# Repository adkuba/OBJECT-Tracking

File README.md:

# OBJECTTracking

### Table of Contents
1. [What I've learned?](#what-Ive-learned)
2. [Android application](#android-application)
3. [IOS Application](#ios-application)
4. [Machine learning](#ml)
5. [Hardware](#hardware)
6. [Electronic board](#electronic-board)

## What I've learned?
* How to use **machine learning** to detect, track objects. How to build and train your own machine learning model and evolutional model. (**Python, Tensorflow, UnityML**)
* Building my own **Android** application that uses machine learning and camera. (**Java, Android Studio**)
* How to build simple **IOS** application that uses built in and external machine learning models, bluetooth and camera. (**Swift, XCode, OpenCV**)
* How to develop from the ground up, special **electronic board** that uses bluetooth. (**Silicon Labs, C**)

#### [Android application](APPS/Android/)
In Java works with SDK wersion 28 - Android 9. Application uses tensorflow model to detect objects and allows user to record videos from the camera. You can also click on object and it shows all the pictures of the same category objects in frame. Good base for developing visual machine learning solutions. <br>
Some errors with older Huawei phones. Optimalization [posibilities](https://developers.google.com/ml-kit/). I also share compressed (quantitized) Tensorflow lite model in application resources folder. (*ssd_mobilenet_v2_quantized_coco*)

#### [IOS application](APPS/IOS/)
IOS application. Compiled OpenCV 4.0.0 framework with trackers avaiable [here](https://www.dropbox.com/s/0iqwqfjz95ehut5/opencv2.framework.zip?dl=0) add it to Frameworks in XCode project settings. You can compile framework yourself following tutorial in official page but remember to add tracking package! Framework should be in main project folder (CamTracking2), can be changed in build settings. You can also follow this [tutorial](https://medium.com/@yiweini/opencv-with-swift-step-by-step-c3cc1d1ee5f1) Aplication allows to test OpenCV trackers, connect to Bluetooth devices and record videos. No suport for Vision tracking so far.

#### [ML](ML/)
Machine learning. Folder with files for creating special object comparison net, running different nets and collecting data. Everything using Keras and Tensorflow. Useful as example to work with.
* **[my_net.py](ML/my_net.py)** <br>
Using keras you can quickly create, train and deploy ready to use model of special net. It is developed for comparing the similarity of two pictures. I also share trained model on car pictures. Aproximately 5k images, 85% accuracy, 350 epochs. 

* **[data.py](ML/data.py)** <br>
Script in python using OpenCV to create set of 2 images either similar or different from video file. All commands in terminal. It needs preprocessed video to display pictures - file *process.py* uses Tensorflow model *mask_rcnn_inception_v2_coco*. Shows pictures of desired category objects from one frame and next. User needs to point which are similar, sets are created automaticly. Screenshot below - second picture.
* **[webpage](ML/webpage/)** <br>
Simple webpage that enables data collection similar to data.py but with progress save. Some improvements can be done. It needs preprocessed video to display pictures - file *process.py*. Webpage creates text file that should look like that 1-2,2-1 it means the same objects are 1 from first picture and 2 from second, 2 from first and 1 from second. Bad matches are created automaticly. Then we can create set of images with *webdecoder.py*. Folder structure without pictures as in repository. Screenshot below - first picture.
* **[run.py](ML/run.py)** <br>
File containing code for running different kinds of neural nets. Mask rcnn object detection, mobilenet_v2 classifier, ssd mobilenet_v2 object detector and Tensorflow Lite model.

#### 

#### Hardware

Simple device to use with mobile phones. All parts were designed in Inventor Proffesional and then 3D printed. Lower part has special thread used in almost all photography devices. We can easily mount it to, for example tripod. Inside the device, is place for all the electronics. I choosed Arduino Nano, Bluetooth for connection and stepper motor. The last one was a mistake. Much better would be the brushless motor used widely in camera gimbals. Upper part has a simple mount for smartphones, wich works with almost all models.

#### [Electronic board](ELECTRONIC-BOARD/)

Using Silicon Labs chip I developed special electronic board that uses Bluetooth. The goal was to implement [AoA in Bluetooth 5.1](https://www.silabs.com/products/wireless/learning-center/bluetooth/bluetooth-direction-finding), but unfortunatelly I wasn't able to achieve that. However I learned how to project board using Eagle from Autodesk and low level programing in Silicon Labs and C. Read [board.pdf](https://github.com/adkuba/OBJECTTracking/blob/master/board.pdf) to learn more about the idea.

Icons credits: 
[link1](https://www.flaticon.com/authors/freepik) 
[link2](https://www.flaticon.com/authors/pause08) 
[link3](https://www.flaticon.com/authors/smashicons)

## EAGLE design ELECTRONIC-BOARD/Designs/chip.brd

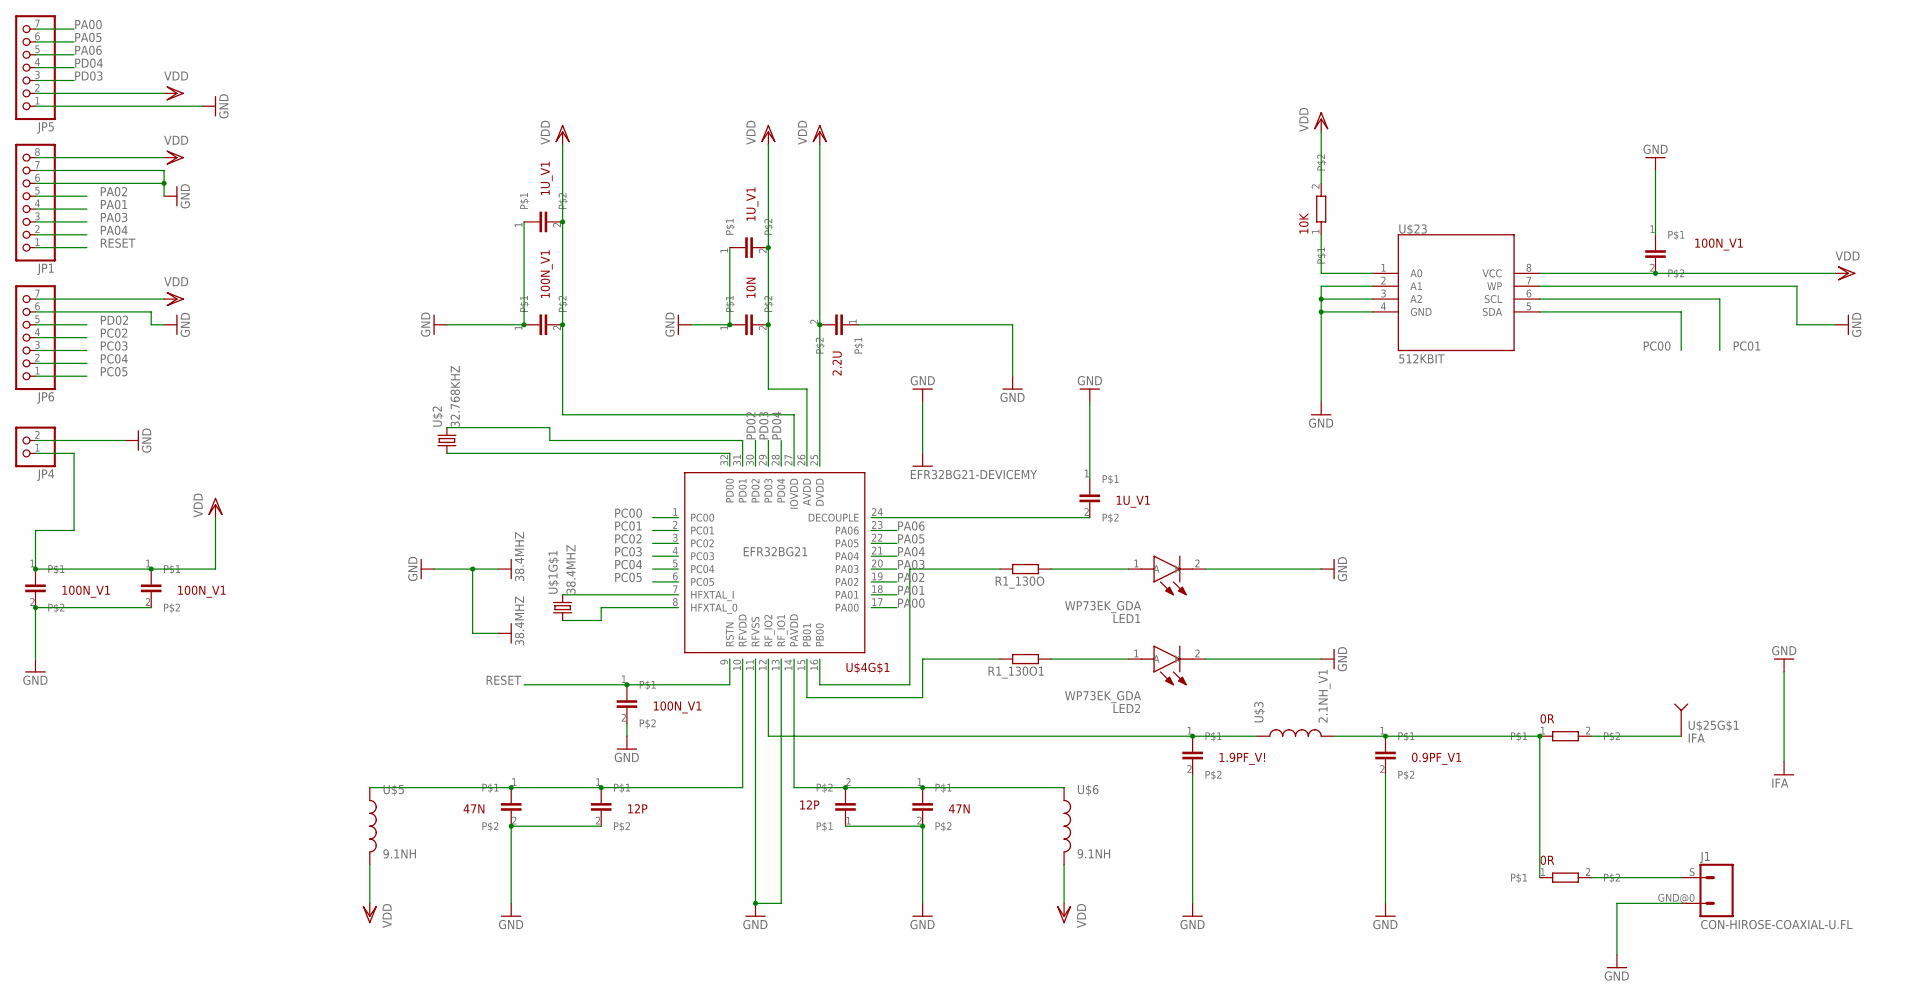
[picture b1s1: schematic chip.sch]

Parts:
J1: CON-HIROSE-COAXIAL-U.FL; CON-U.FL
JP1: PINHD-1X8; 1X08
JP4: PINHD-1X2; 1X02
JP5, JP6: PINHD-1X7; 1X07
LED1, LED2: WP73EK_GDA; WP73EKGDA
R1_130O, R1_130O1: R-EU_0204/7; 0204/7
U$1: 38.4MHZ; OSCCC200X160X40N
U$2: 32.768KHZ; RESC3213X90N
U$3: 2.1NH_V1; INDC0402X30N
U$4: EFR32BG21-DEVICEMY; QFN40P400X400X90-33T270N
U$5, U$6: 9.1NH; INDC0603X40N
U$7, U$8, U$9, U$10, U$22: 100N_V1; CAPC2012X78N
U$11: 0.9PF_V1; CAPC1005X50N
U$12: 1.9PF_V!; CAPC1005X50N
U$13, U$14: 47N; CAPC2012X78N
U$15, U$16: 12P; CAPC1005X50N
U$17: 2.2U; CAPC2012X125N
U$18, U$19, U$20: 1U_V1; CAPC2012X125N
U$21: 10N; CAPC2012X78N
U$23: 512KBIT; SOIC127P599X175-8N
U$24: 10K; RESC3213X90N
U$25: IFA
U$26, U$27: 0R; RESC3213X90N

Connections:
GND: J1.GND@0 (2), JP1.6, JP1.7, JP4.2, JP5.1, JP6.6, LED1.2 (K), LED2.2 (K), U$1.2 (GND), U$1.4 (GND), U$4.11 (RFVSS), U$4.13 (RF_IO1), U$4.33 (GND), U$7.2, U$8.1, U$9.1, U$10.2, U$11.2, U$12.2, U$13.2, U$14.2, U$15.2, U$16.1, U$17.1, U$18.1, U$19.1, U$20.1, U$21.1, U$22.2, U$23.2 (A1), U$23.3 (A2), U$23.4 (GND), U$23.7 (WP), U$25.P$2 (GND)
unnamed: U$1.3 (2), U$4.7 (HFXTAL_I)
unnamed: U$1.1, U$4.8 (HFXTAL_0)
unnamed: LED1.1 (A), R1_130O.1
unnamed: U$4.14 (PAVDD), U$6.1, U$14.1, U$16.2
unnamed: U$4.10 (RFVDD), U$5.1, U$13.1, U$15.1
unnamed: U$3.1, U$4.12 (RF_IO2), U$12.1
unnamed: U$3.2, U$11.1, U$26.1, U$27.1
unnamed: J1.S (1), U$27.2
unnamed: U$25.P$1 (ANTENNA), U$26.2
unnamed: U$4.24 (DECOUPLE), U$19.2
unnamed: U$2.2, U$4.31 (PD01)
unnamed: U$2.1, U$4.32 (PD00)
unnamed: LED2.1 (A), R1_130O1.1
unnamed: R1_130O.2, U$4.16 (PB00)
unnamed: R1_130O1.2, U$4.15 (PB01)
unnamed: U$23.1 (A0), U$24.1
PA00: JP5.7, U$4.17 (PA00)
PA01: JP1.4, U$4.18 (PA01)
PA02: JP1.5, U$4.19 (PA02)
PA03: JP1.3, U$4.20 (PA03)
PA04: JP1.2, U$4.21 (PA04)
PA05: JP5.6, U$4.22 (PA05)
PA06: JP5.5, U$4.23 (PA06)
PC00: U$4.1 (PC00), U$23.5 (SDA)
PC01: U$4.2 (PC01), U$23.6 (SCL)
PC02: JP6.4, U$4.3 (PC02)
PC03: JP6.3, U$4.4 (PC03)
PC04: JP6.2, U$4.5 (PC04)
PC05: JP6.1, U$4.6 (PC05)
PD02: JP6.5, U$4.30 (PD02)
PD03: JP5.3, U$4.29 (PD03)
PD04: JP5.4, U$4.28 (PD04)
RESET: JP1.1, U$4.9 (RSTN), U$10.1
VDD: JP1.8, JP4.1, JP5.2, JP6.7, U$4.25 (DVDD), U$4.26 (AVDD), U$4.27 (IOVDD), U$5.2, U$6.2, U$7.1, U$8.2, U$9.2, U$17.2, U$18.2, U$20.2, U$21.2, U$22.1, U$23.8 (VCC), U$24.2

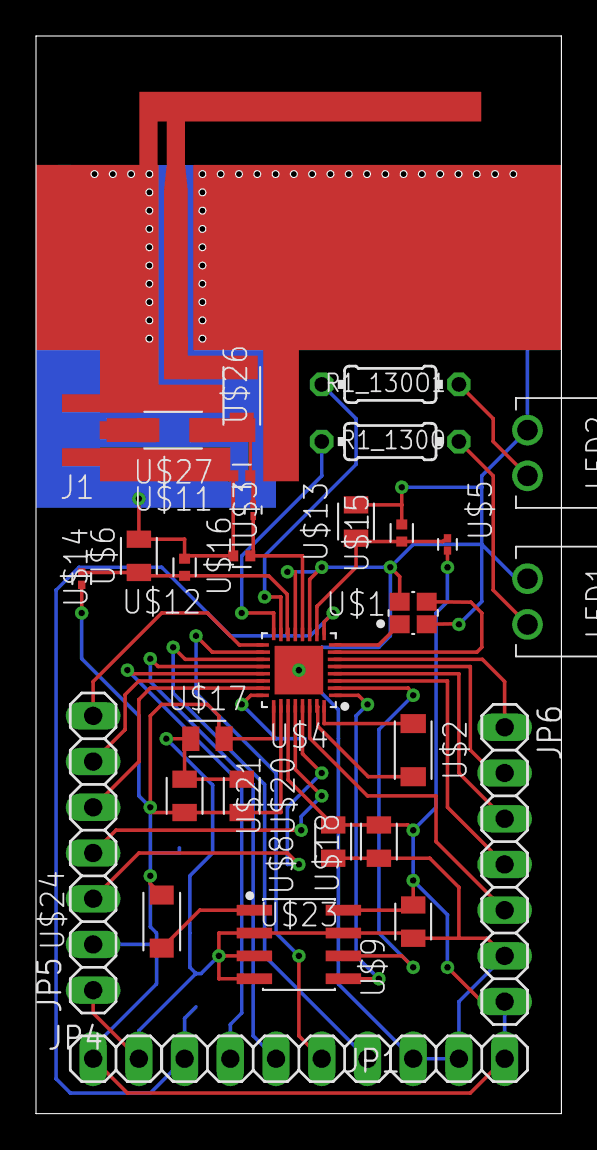
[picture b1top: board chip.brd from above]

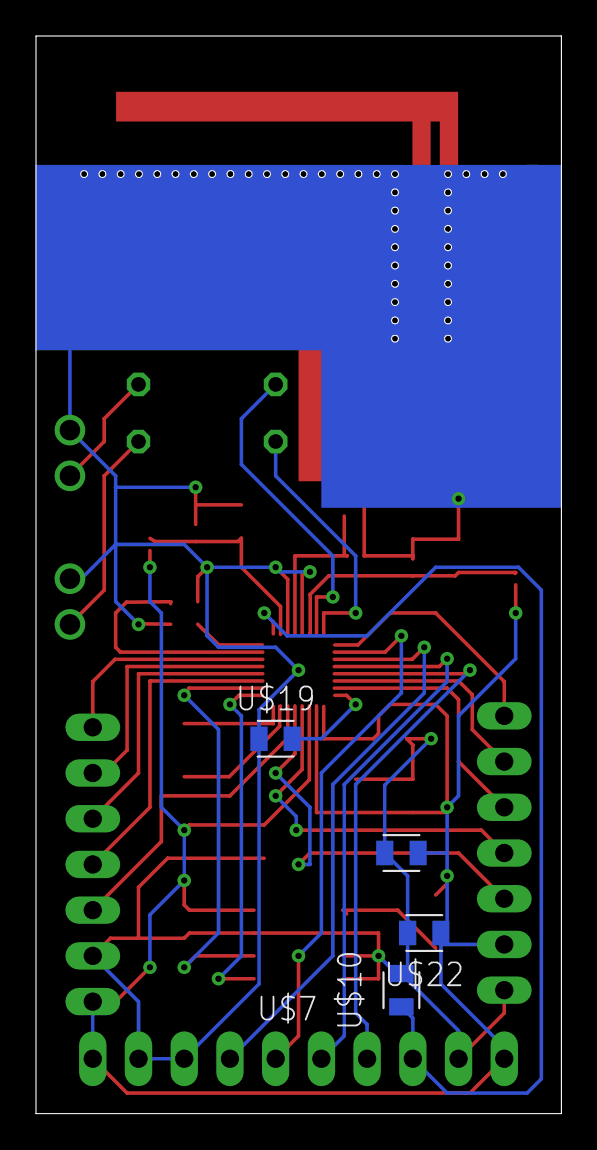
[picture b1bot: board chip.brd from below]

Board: 2 copper layers, 29.2 x 59.9 mm, 36 parts (4 on the bottom side), 35 nets.

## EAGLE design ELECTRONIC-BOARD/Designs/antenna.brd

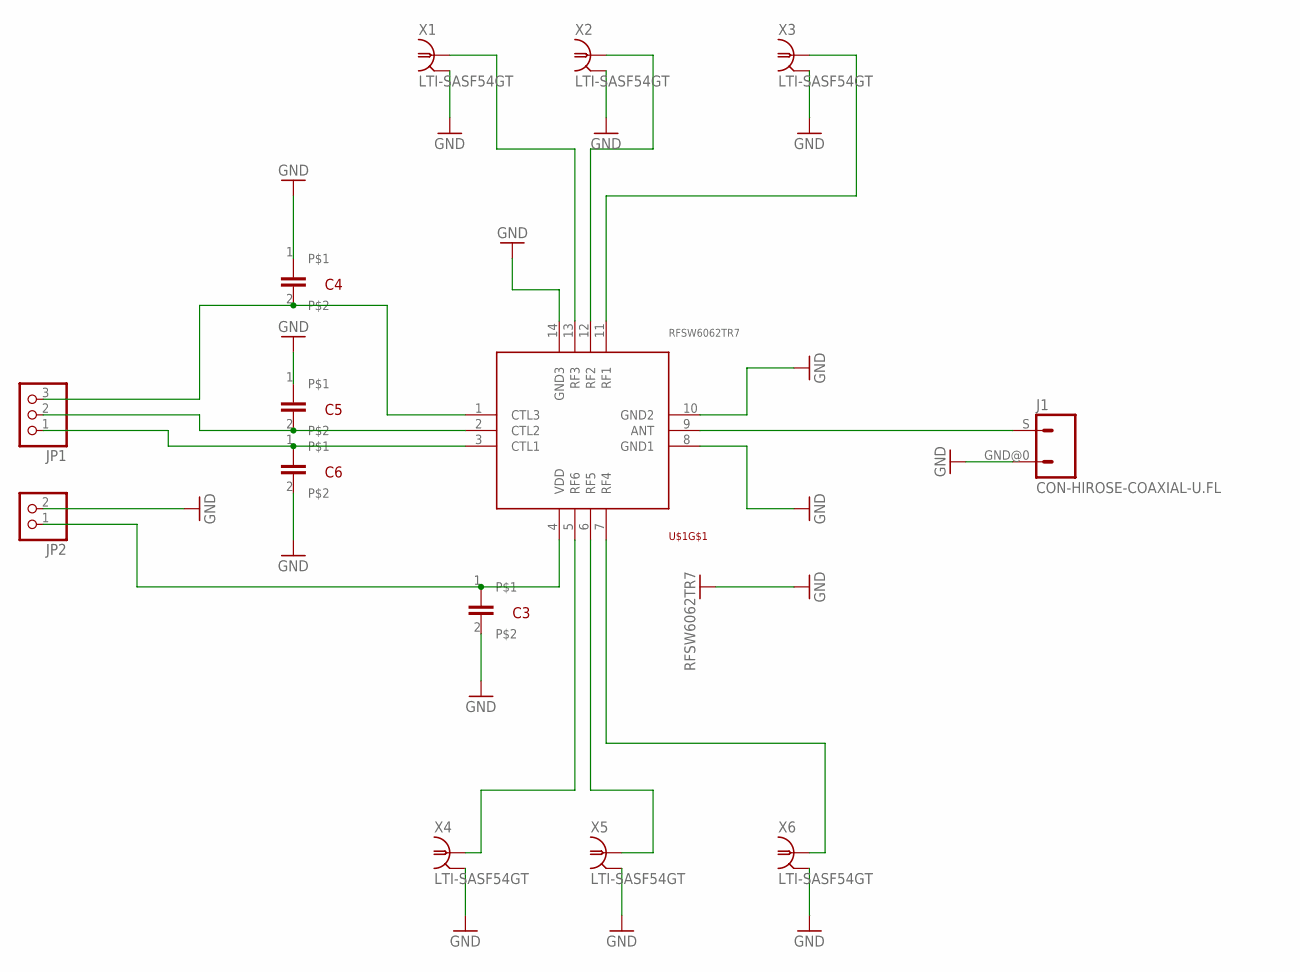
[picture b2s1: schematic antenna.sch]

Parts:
C3: C3_0.01µF; CAPC2012X78N
C4, C5, C6: C8_100PF; CAPC2012X78N
J1: CON-HIROSE-COAXIAL-U.FL; CON-U.FL
JP1: PINHD-1X3; 1X03
JP2: PINHD-1X2; 1X02
U$1: RFSW6062TR7; QFN40P200X200X55-15T98N
X1, X2, X3, X4, X5, X6: LTI-SASF54GT

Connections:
GND: C3.2, C4.1, C5.1, C6.2, J1.GND@0 (2), JP2.2, U$1.8 (GND1), U$1.10 (GND2), U$1.14 (GND3), U$1.15 (GND), X1.2, X1.3 (2), X1.4 (2), X1.5 (2), X2.2, X2.3 (2), X2.4 (2), X2.5 (2), X3.2, X3.3 (2), X3.4 (2), X3.5 (2), X4.2, X4.3 (2), X4.4 (2), X4.5 (2), X5.2, X5.3 (2), X5.4 (2), X5.5 (2), X6.2, X6.3 (2), X6.4 (2), X6.5 (2)
unnamed: J1.S (1), U$1.9 (ANT)
unnamed: C4.2, JP1.3, U$1.1 (CTL3)
unnamed: C5.2, JP1.2, U$1.2 (CTL2)
unnamed: C6.1, JP1.1, U$1.3 (CTL1)
unnamed: U$1.5 (RF6), X4.1
unnamed: U$1.6 (RF5), X5.1
unnamed: U$1.7 (RF4), X6.1
unnamed: U$1.13 (RF3), X1.1
unnamed: U$1.12 (RF2), X2.1
unnamed: U$1.11 (RF1), X3.1
unnamed: C3.1, JP2.1, U$1.4 (VDD)

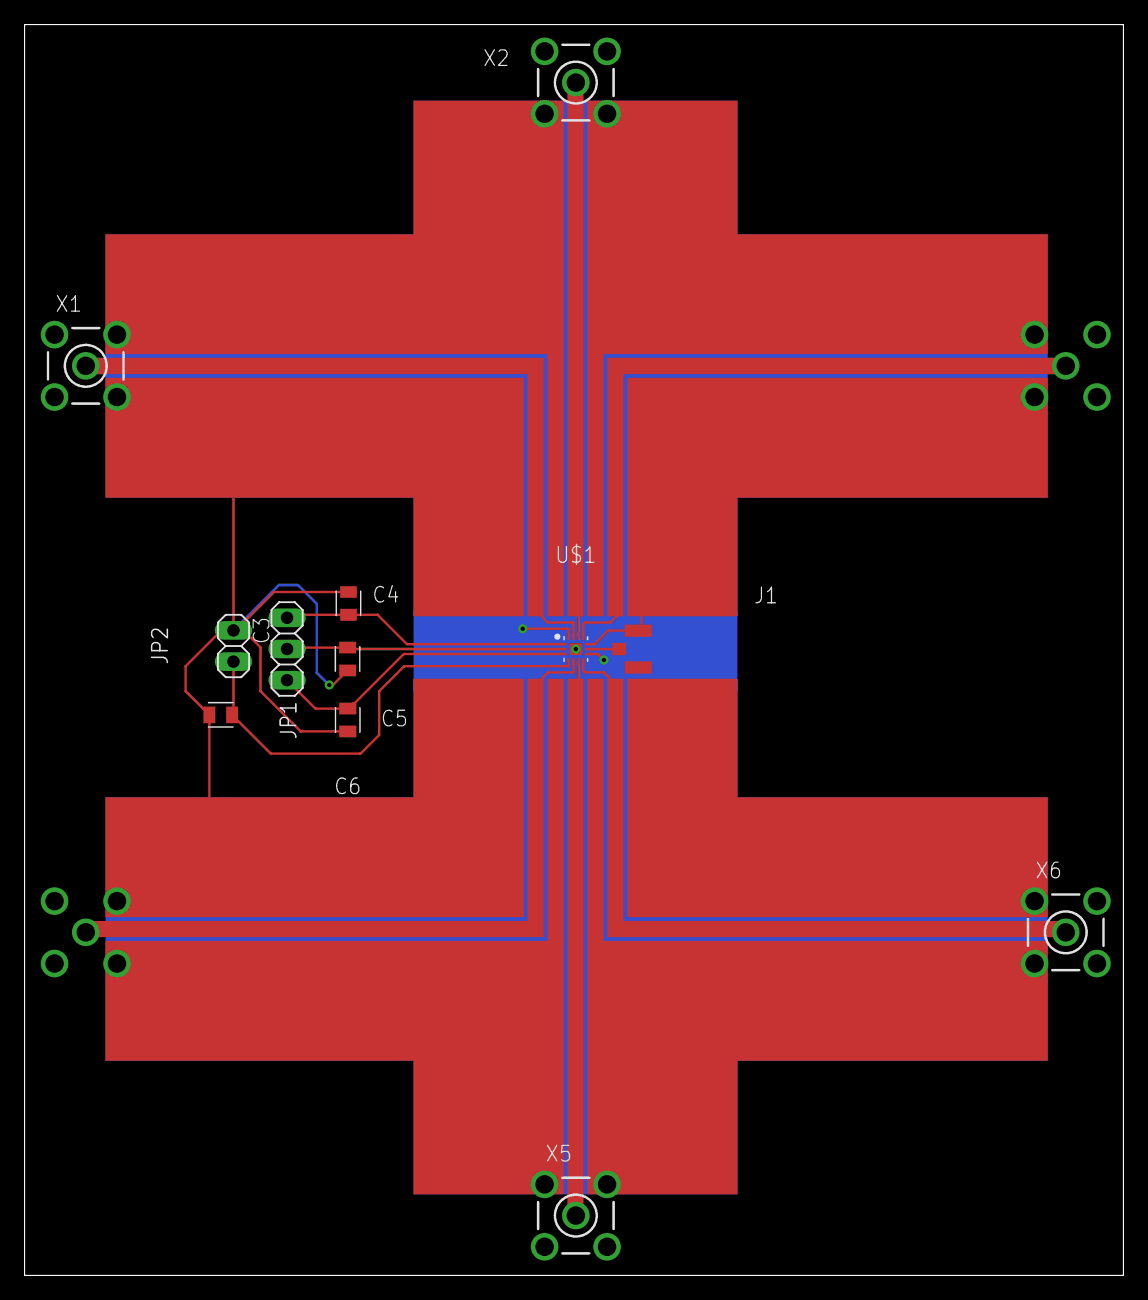
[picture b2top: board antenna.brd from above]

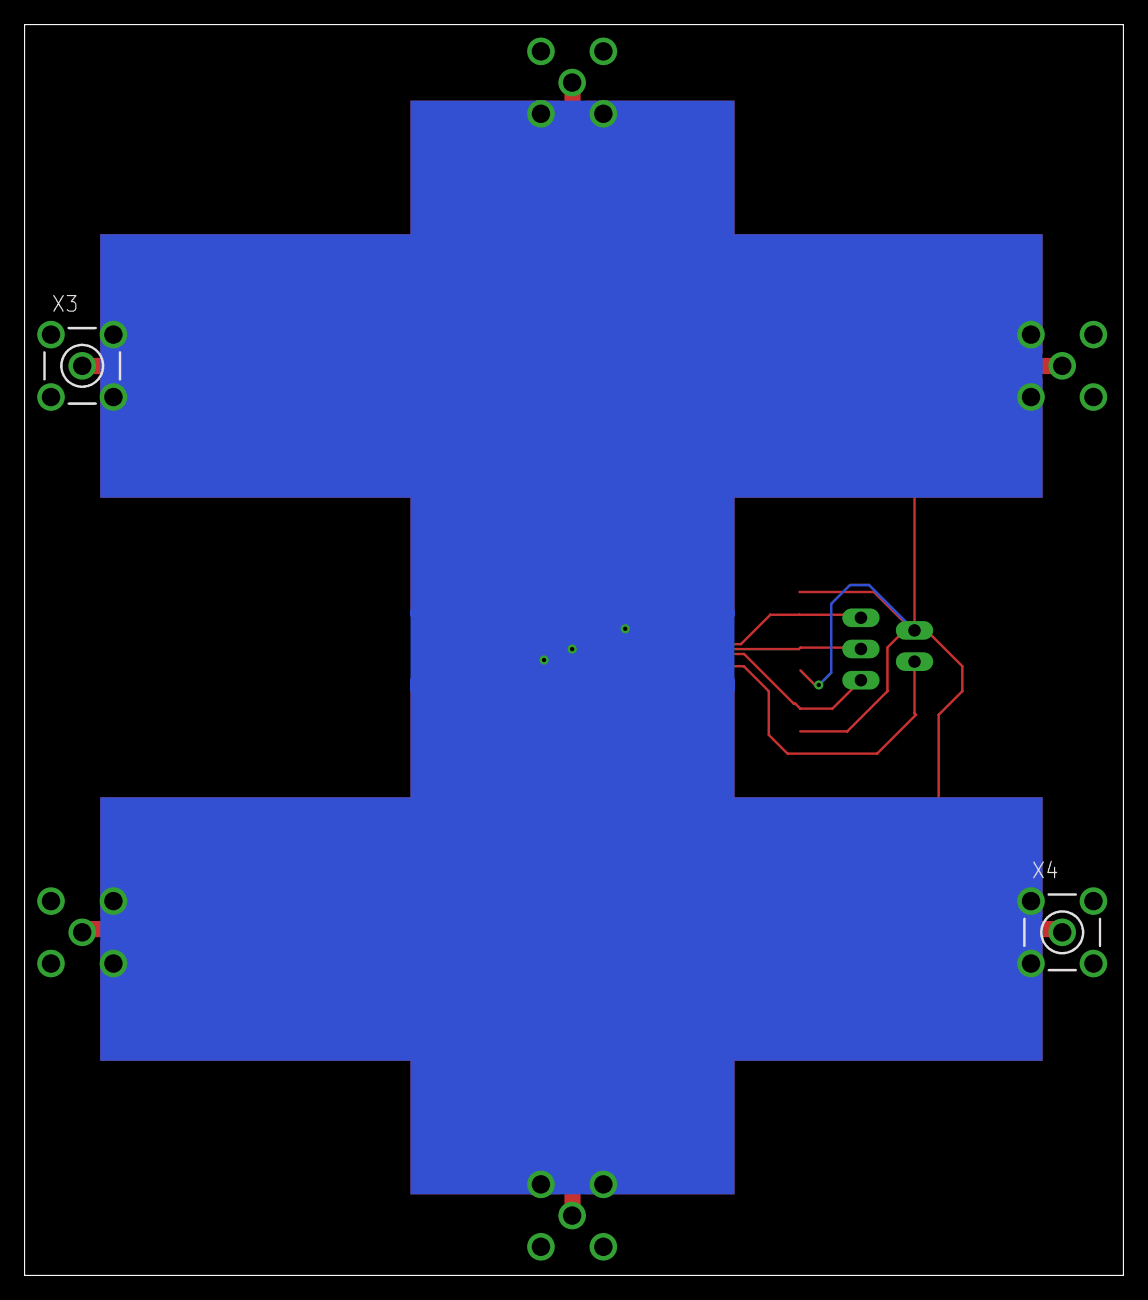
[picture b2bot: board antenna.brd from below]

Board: 2 copper layers, 89.4 x 101.8 mm, 14 parts (2 on the bottom side), 12 nets.

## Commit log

2019-09-30 android app added
2019-10-01 adding
2019-10-04 further work
2019-10-05 first ios version
2019-10-05 ios first redo
2019-10-05 IOS app RC
2019-10-05 DS Store rm
2019-10-17 add hardware.jpg
2019-10-17 compressed
2019-10-17 compression2
2020-04-16 Setup #1
    utworzenie projektu, utworzenie poczatkowego srodowiska
2020-04-25 Closes #1
    ready to cloud training
2020-04-30 config added
    czekam na wyniki uczenia
2020-04-30 SNNET merge
    old tests1
2020-04-30 old_tests2
    rest of the files
2020-09-16 Chip update
2020-09-16 chip-images
2020-09-16 electronic-board
2020-09-23 readme-update
2020-09-23 fixes-readme
2020-09-23 links-fix

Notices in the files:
parts and their libraries:
m-pad-2.1: License : GNU General Public License version 2 (see bottom)
